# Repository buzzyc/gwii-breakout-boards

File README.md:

# G-Wii Breakout Boards

Custom KiCad breakout PCBs designed for the **G-Wii portable Wii** project. These boards replace the dozens of individual signal wires typically needed between the two halves of a portable Wii build with clean, modular PCBs and FFC (flat flex cable) connections.

Built in **KiCad 9.0**.

## Boards

### Daughterboard (`Daughterboard/`)
The central connector hub. Interfaces with the trimmed Wii motherboard and consolidates all control, audio, and video signals into organized connectors. Features a **GC+2.0** controller interface IC and a **UAMP** audio amplifier, routing button inputs (A/B/X/Y/Z, D-pad, triggers), analog stick axes, and stereo audio through a single interconnect system.

### Video FLX (`Video_FLX/`)
Video and signal breakout board that routes RGB video (RED, GREEN, BLUE), sync signals (H-Sync, V-Sync), audio lines, and control signals between the two halves of the portable via FFC cables — replacing what would otherwise be 20–30 individual wires.

### ABXY (`ABXY/`)
Face button PCB for the A, B, X, Y, and Z buttons. Uses ALPS SKEYACA010 tactile switches and routes all button signals through a 6-pin connector back to the daughterboard. Also includes a mount for a common-anode tricolour (RGB) LED.

### D-Pad (`DPAD/`)
Directional pad button PCB for Up, Down, Left, and Right inputs.

### Joystick (`joystick/`)
Analog joystick breakout board. Provides connectors for joystick axis signals and mounting, routing back to the daughterboard.

### Tactile Mount (`tactmount/`)
Tactile switch mounting board for auxiliary controls (Start, Select, Home, volume, etc.). Includes signal conditioning with pull-up resistors and decoupling capacitors.

The footprint labelled **SYNC** can act as either **SOURCE** or **Bluetooth sync** button depending on jumper configuration — position both jumpers at **1&2** for video source, or **2&3** for BT sync.

The resistor ladder on this board is designed around the **ZJ050NA-08C-KYV-N2** black VGA driver board (board reference](https://bitbuilt.net/forums/threads/resistor-value.6798/)).

## Shared Libraries

- **`4LAYER_FOOTPRINTS.pretty`** — Custom footprints for 4LayerTech components (GC+2.0, PMS, UAMP, etc.)
- **`4LAYER_SCHEMATIC_SYMBOLS`** — Matching schematic symbols
- **`ALPS.pretty`** — ALPS SKEYACA010 tactile switch footprint (custom library — **note:** one of the GND pads is on the wrong side in the current footprint)

## Project Context

The [G-Wii](https://bitbuilt.net/forums/) is a portable Wii console build from the [BitBuilt](https://bitbuilt.net/) community. It uses a trimmed Wii motherboard fitted into a custom handheld case. These breakout boards make wiring significantly cleaner and more reliable by consolidating signals onto PCBs connected via FFC cables.

## License

Open hardware — use and modify freely for your own portable Wii builds.

> **Note:** These boards are not perfect and are provided as-is. You are more than welcome to modify them to suit your build.

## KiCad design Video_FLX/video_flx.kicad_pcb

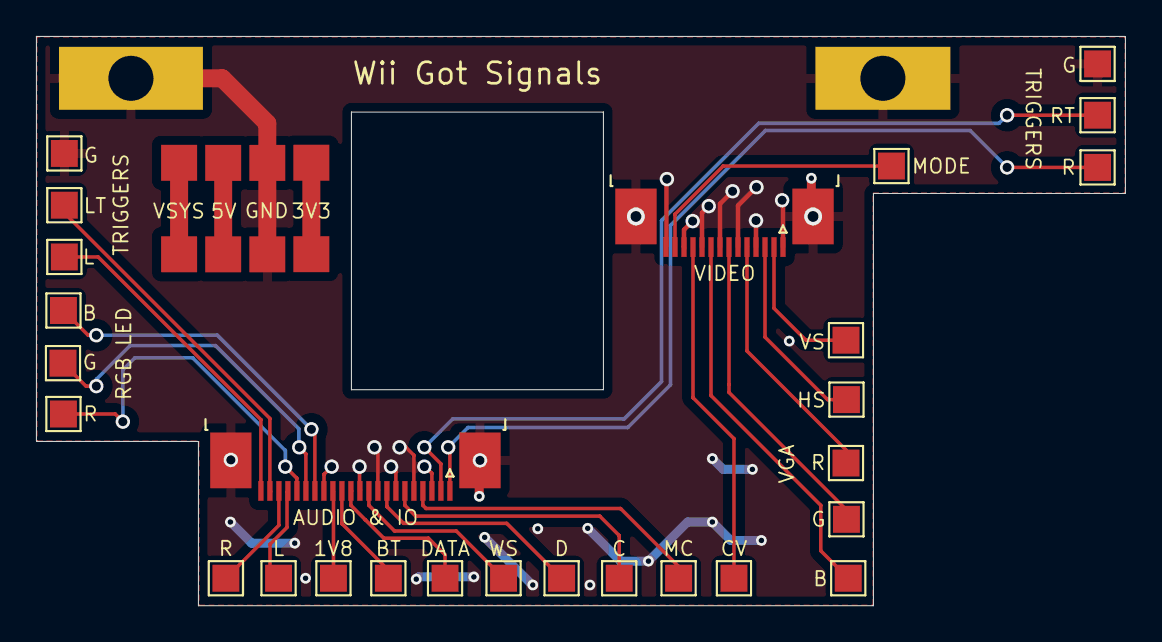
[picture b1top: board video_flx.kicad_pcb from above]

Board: 2 copper layers, 60.5 x 31.6 mm, 27 parts (0 on the bottom side), 24 nets.

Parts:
1V8: TEST_1P; TestPoint_Pad_1.5x1.5mm
AUDIO & IO: Conn_01x16_MountingPin; TE_2-1734839-2_1x22-1MP_P0.5mm_Horizontal
B: TEST_1P; TestPoint_Pad_1.5x1.5mm
B#2: TEST_1P; TestPoint_Pad_1.5x1.5mm
BT: TEST_1P; TestPoint_Pad_1.5x1.5mm
C: TEST_1P; TestPoint_Pad_1.5x1.5mm
CV: TEST_1P; TestPoint_Pad_1.5x1.5mm
D: TEST_1P; TestPoint_Pad_1.5x1.5mm
DATA: TEST_1P; TestPoint_Pad_1.5x1.5mm
G: TEST_1P; TestPoint_Pad_1.5x1.5mm
G#2, G#3, G#4: TEST_1P; TestPoint_Pad_1.5x1.5mm
HS: TEST_1P; TestPoint_Pad_1.5x1.5mm
L: TEST_1P; TestPoint_Pad_1.5x1.5mm
L#2: TEST_1P; TestPoint_Pad_1.5x1.5mm
LT: TEST_1P; TestPoint_Pad_1.5x1.5mm
MC: TEST_1P; TestPoint_Pad_1.5x1.5mm
MODE: TEST_1P; TestPoint_Pad_1.5x1.5mm
R: TEST_1P; TestPoint_Pad_1.5x1.5mm
R#2, R#3, R#4: TEST_1P; TestPoint_Pad_1.5x1.5mm
RT: TEST_1P; TestPoint_Pad_1.5x1.5mm
VIDEO: Conn_01x14_MountingPin; TE_1-1734839-4_1x14-1MP_P0.5mm_Horizontal
VS: TEST_1P; TestPoint_Pad_1.5x1.5mm
WS: TEST_1P; TestPoint_Pad_1.5x1.5mm

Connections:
+1V8: 1V8.1, AUDIO & IO.14
BLUE: B.1, VIDEO.9
BT: AUDIO & IO.13, BT.1
C: AUDIO & IO.6, C.1
CDATA: AUDIO & IO.12, DATA.1
CV: CV.1, VIDEO.11
D: AUDIO & IO.8, D.1
GND: AUDIO & IO.3, AUDIO & IO.5, AUDIO & IO.7, AUDIO & IO.9, AUDIO & IO.11, AUDIO & IO.15, AUDIO & IO.MP (MountPin), G#2.1, G#4.1, VIDEO.1, VIDEO.4, VIDEO.6, VIDEO.8, VIDEO.10, VIDEO.12, VIDEO.14, VIDEO.MP (MountPin)
GREEN: G#3.1, VIDEO.7
HS: HS.1, VIDEO.3
L: AUDIO & IO.19, L.1
LA: AUDIO & IO.22, L#2.1
LEDB: AUDIO & IO.16, B#2.1
LEDG: AUDIO & IO.17, G.1
LEDR: AUDIO & IO.18, R#2.1
LT: AUDIO & IO.21, LT.1
MC: AUDIO & IO.4, MC.1
MODE: MODE.1, VIDEO.13
R: AUDIO & IO.20, R#3.1
RA: AUDIO & IO.1, R.1
RED: R#4.1, VIDEO.5
RT: AUDIO & IO.2, RT.1
VS: VIDEO.2, VS.1
WS: AUDIO & IO.10, WS.1

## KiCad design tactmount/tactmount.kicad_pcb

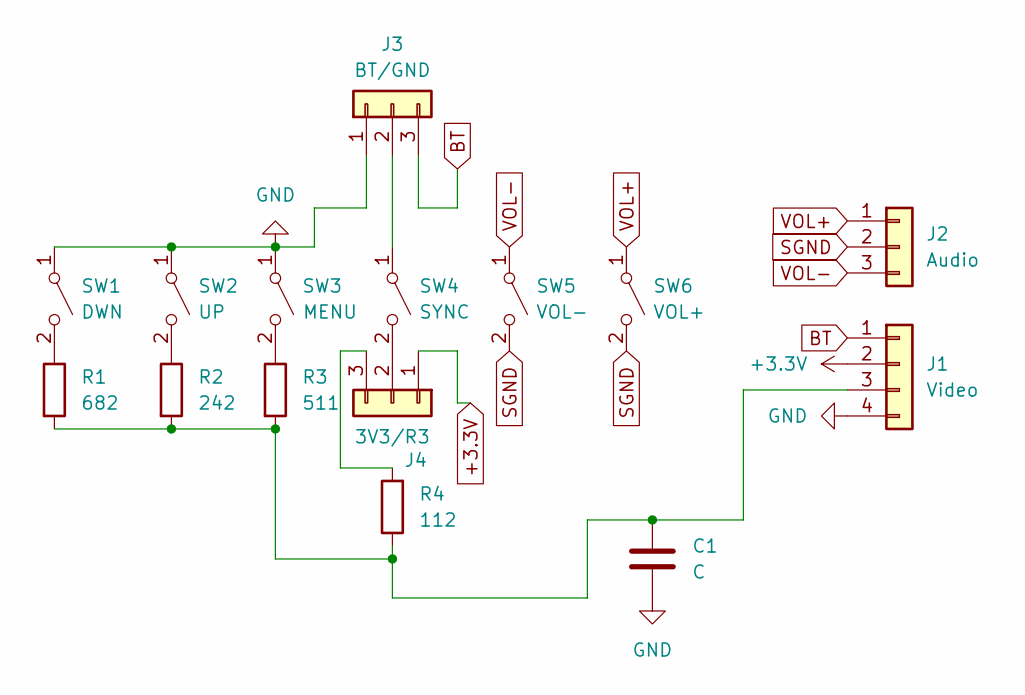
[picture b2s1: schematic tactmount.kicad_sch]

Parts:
C1: C; C_0603_1608Metric_Pad1.08x0.95mm_HandSolder
J1: Video; SolderWire-0.1sqmm_1x04_P3.6mm_D0.4mm_OD1mm
J2: Audio; SolderWire-0.1sqmm_1x03_P3.6mm_D0.4mm_OD1mm
J3: BT/GND; PinHeader_1x03_P2.54mm_Vertical
J4: 3V3/R3; PinHeader_1x03_P2.54mm_Vertical
R1: 682; R_0603_1608Metric_Pad0.98x0.95mm_HandSolder
R2: 242; R_0603_1608Metric_Pad0.98x0.95mm_HandSolder
R3: 511; R_0603_1608Metric_Pad0.98x0.95mm_HandSolder
R4: 112; R_0603_1608Metric_Pad0.98x0.95mm_HandSolder
SW1: DWN; SW_PUSH_6mm_H7.3mm
SW2: UP; SW_PUSH_6mm_H7.3mm
SW3: MENU; SW_PUSH_6mm_H7.3mm
SW4: SYNC; SW_PUSH_6mm_H7.3mm
SW5: VOL-; SW_PUSH_6mm_H7.3mm
SW6: VOL+; SW_PUSH_6mm_H7.3mm

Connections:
+3.3V: J1.2, J4.1
BT: J1.1, J3.3
GND: C1.2, J1.4, J3.1, SW1.1 (A), SW2.1 (A), SW3.1 (A)
unnamed: C1.1, J1.3, R1.2, R2.2, R3.2, R4.1
unnamed: J3.2, SW4.1 (A)
unnamed: J4.2, SW4.2 (B)
unnamed: J4.3, R4.2
unnamed: R1.1, SW1.2 (B)
unnamed: R2.1, SW2.2 (B)
unnamed: R3.1, SW3.2 (B)
SGND: J2.2, SW5.2 (B), SW6.2 (B)
VOL+: J2.1, SW6.1 (A)
VOL-: J2.3, SW5.1 (A)

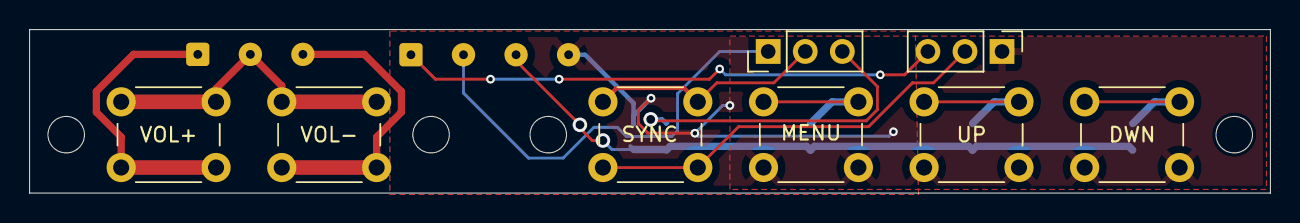
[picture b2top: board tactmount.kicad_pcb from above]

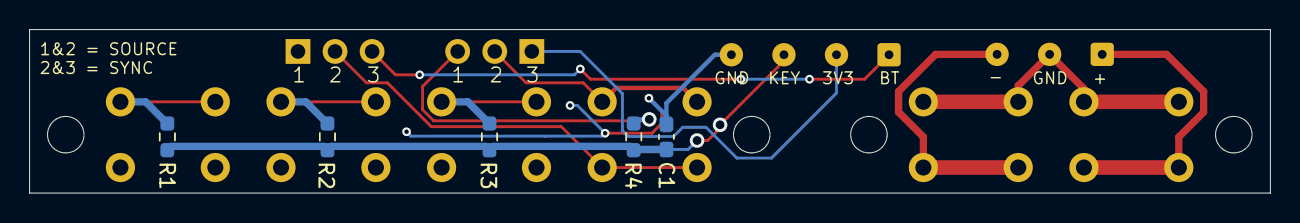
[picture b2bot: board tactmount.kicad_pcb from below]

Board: 2 copper layers, 85.0 x 11.2 mm, 15 parts (5 on the bottom side), 13 nets.

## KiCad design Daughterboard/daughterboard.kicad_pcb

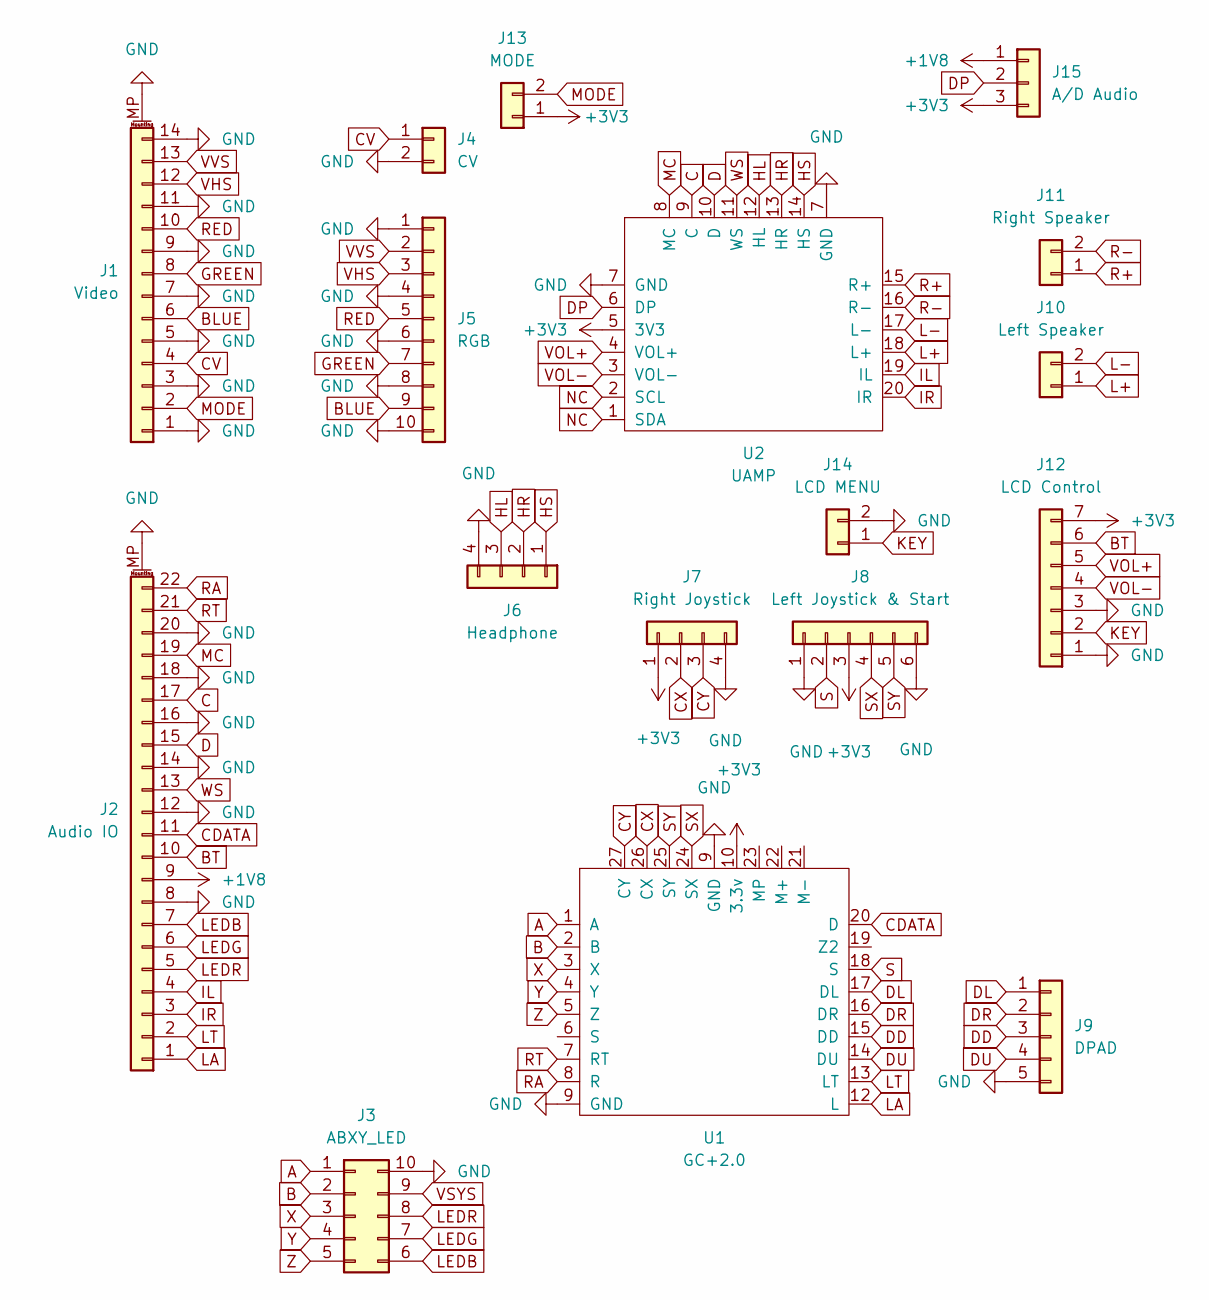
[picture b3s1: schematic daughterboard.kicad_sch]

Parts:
J1: Video; TE_1-1734839-4_1x14-1MP_P0.5mm_Horizontal
J2: Audio IO; TE_2-1734839-2_1x22-1MP_P0.5mm_Horizontal
J3: ABXY_LED; PinSocket_2x05_P2.54mm_Vertical
J4: CV; PinHeader_1x02_P2.54mm_Vertical
J5: RGB; PinSocket_1x10_P2.54mm_Vertical
J6: Headphone; PinSocket_1x04_P2.54mm_Vertical
J7: Right Joystick; PinHeader_1x04_P2.54mm_Vertical
J8: Left Joystick & Start; PinHeader_1x06_P2.54mm_Vertical
J9: DPAD; PinSocket_1x05_P2.54mm_Vertical
J10: Left Speaker; PinHeader_1x02_P2.54mm_Vertical
J11: Right Speaker; PinHeader_1x02_P2.54mm_Vertical
J12: LCD Control; PinHeader_1x07_P2.54mm_Vertical
J13: MODE; PinHeader_1x02_P2.54mm_Vertical
J14: LCD MENU; PinSocket_1x02_P2.54mm_Vertical
J15: A/D Audio; PinHeader_1x03_P2.54mm_Vertical
U1: GC+2.0
U2: UAMP; UAMP2

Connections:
+1V8: J2.9, J15.1
+3V3: J7.1, J8.3, J12.7, J13.1, J15.3, U1.10 (3.3v), U2.5 (3V3)
A: J3.1, U1.1 (A)
B: J3.2, U1.2 (B)
BLUE: J1.6, J5.9
BT: J2.10, J12.6
C: J2.17, U2.9 (C)
CDATA: J2.11, U1.20 (D)
CV: J1.4, J4.1
CX: J7.2, U1.26 (CX)
CY: J7.3, U1.27 (CY)
D: J2.15, U2.10 (D)
DD: J9.3, U1.15 (DD)
DL: J9.1, U1.17 (DL)
DP: J15.2, U2.6 (DP)
DR: J9.2, U1.16 (DR)
DU: J9.4, U1.14 (DU)
GND: J1.1, J1.3, J1.5, J1.7, J1.9, J1.11, J1.14, J1.MP (MountPin), J2.8, J2.12, J2.14, J2.16, J2.18, J2.20, J2.MP (MountPin), J3.10, J4.2, J5.1, J5.4, J5.6, J5.8, J5.10, J6.4, J7.4, J8.1, J8.6, J9.5, J12.1, J12.3, J14.2, U1.9 (GND), U2.7 (GND)
GREEN: J1.8, J5.7
HL: J6.3, U2.12 (HL)
HR: J6.2, U2.13 (HR)
HS: J6.1, U2.14 (HS)
IL: J2.4, U2.19 (IL)
IR: J2.3, U2.20 (IR)
KEY: J12.2, J14.1
L+: J10.1, U2.18 (L+)
L-: J10.2, U2.17 (L-)
LA: J2.1, U1.12 (L)
LEDB: J2.7, J3.6
LEDG: J2.6, J3.7
LEDR: J2.5, J3.8
LT: J2.2, U1.13 (LT)
MC: J2.19, U2.8 (MC)
MODE: J1.2, J13.2
R+: J11.1, U2.15 (R+)
R-: J11.2, U2.16 (R-)
RA: J2.22, U1.8 (R)
RED: J1.10, J5.5
RT: J2.21, U1.7 (RT)
S: J8.2, U1.18 (S)
SX: J8.4, U1.24 (SX)
SY: J8.5, U1.25 (SY)
VHS: J1.12, J5.3
VOL+: J12.5, U2.4 (VOL+)
VOL-: J12.4, U2.3 (VOL-)
VSYS: J3.9
VVS: J1.13, J5.2
WS: J2.13, U2.11 (WS)
X: J3.3, U1.3 (X)
Y: J3.4, U1.4 (Y)
Z: J3.5, U1.5 (Z)

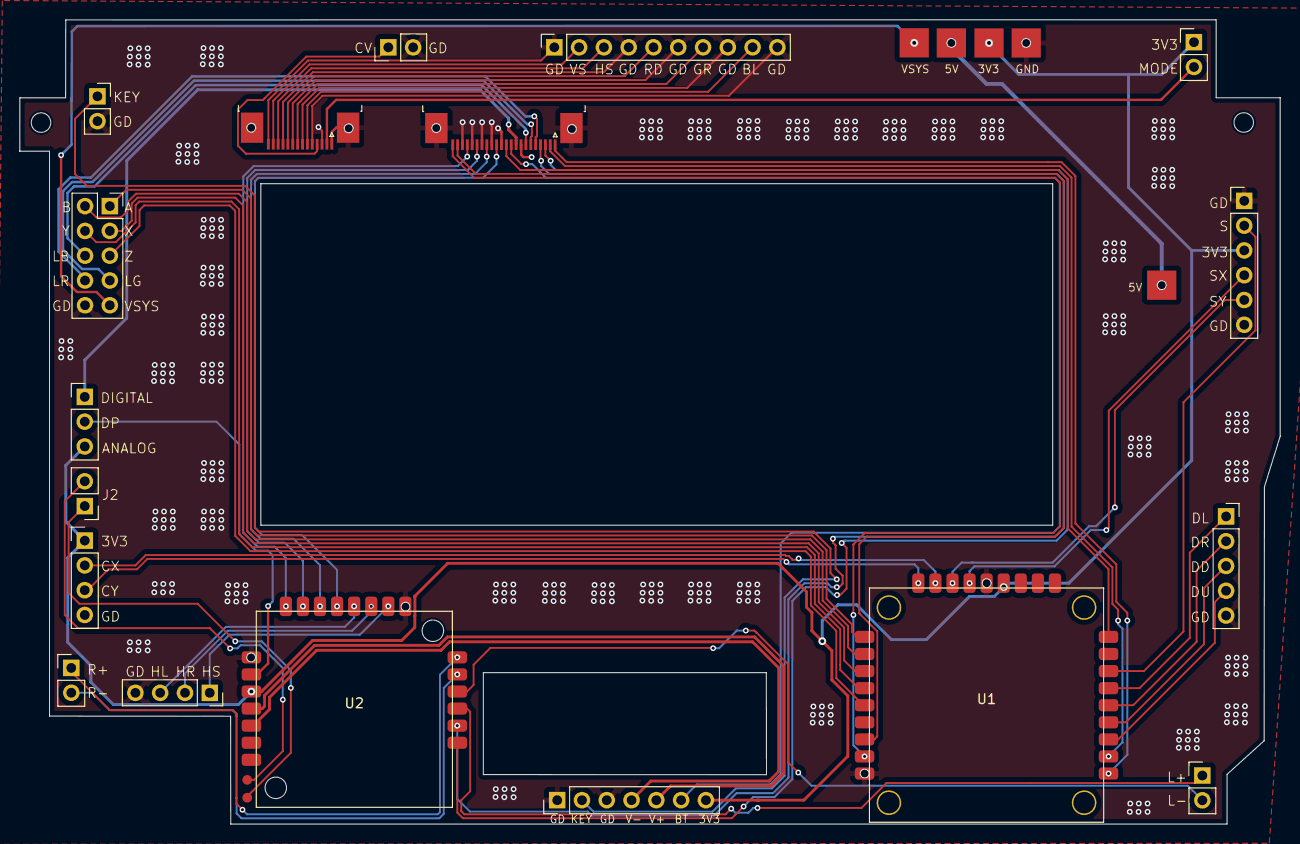
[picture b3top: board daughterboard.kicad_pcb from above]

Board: 2 copper layers, 129.2 x 82.4 mm, 18 parts (0 on the bottom side), 50 nets.

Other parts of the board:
J11#2: Right Speaker; PinHeader_1x02_P2.54mm_Vertical

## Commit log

2026-04-08 Initial commit: G-Wii breakout board KiCad projects
    Custom breakout PCBs for the G-Wii portable Wii build.
    Replaces 20-30 individual signal wires with modular PCBs and FFC cables.
    Boards included:
    - Daughterboard: Central connector hub with GC+2.0 and UAMP
    - Video FLX: Video/audio signal routing via FFC cables
    - ABXY: Face button PCB (A/B/X/Y/Z)
2026-04-08 Add PCB render images and update README
    - Add daughterboard and Video FLX board renders
    - Note ABXY board includes tricolour LED mount (common anode)
    - Note ALPS footprint GND pad issue
2026-04-08 Add remaining board images and update README
    - Add renders for ABXY, DPAD, joystick, and tactmount (front/rear)
    - Document tactmount SYNC/BT sync jumper configuration
    - Note resistor ladder designed for ZJ050NA-08C VGA driver board
    - Add open modification disclaimer
2026-04-08 Update tactmount resistor ladder reference to correct thread
2026-04-08 Fix markdown link formatting in README.md
2026-04-08 Clarify SYNC footprint functionality in README
    Updated the description of the SYNC footprint to clarify its dual functionality.
2026-04-08 Correct spelling of 'SOURCE' in README
